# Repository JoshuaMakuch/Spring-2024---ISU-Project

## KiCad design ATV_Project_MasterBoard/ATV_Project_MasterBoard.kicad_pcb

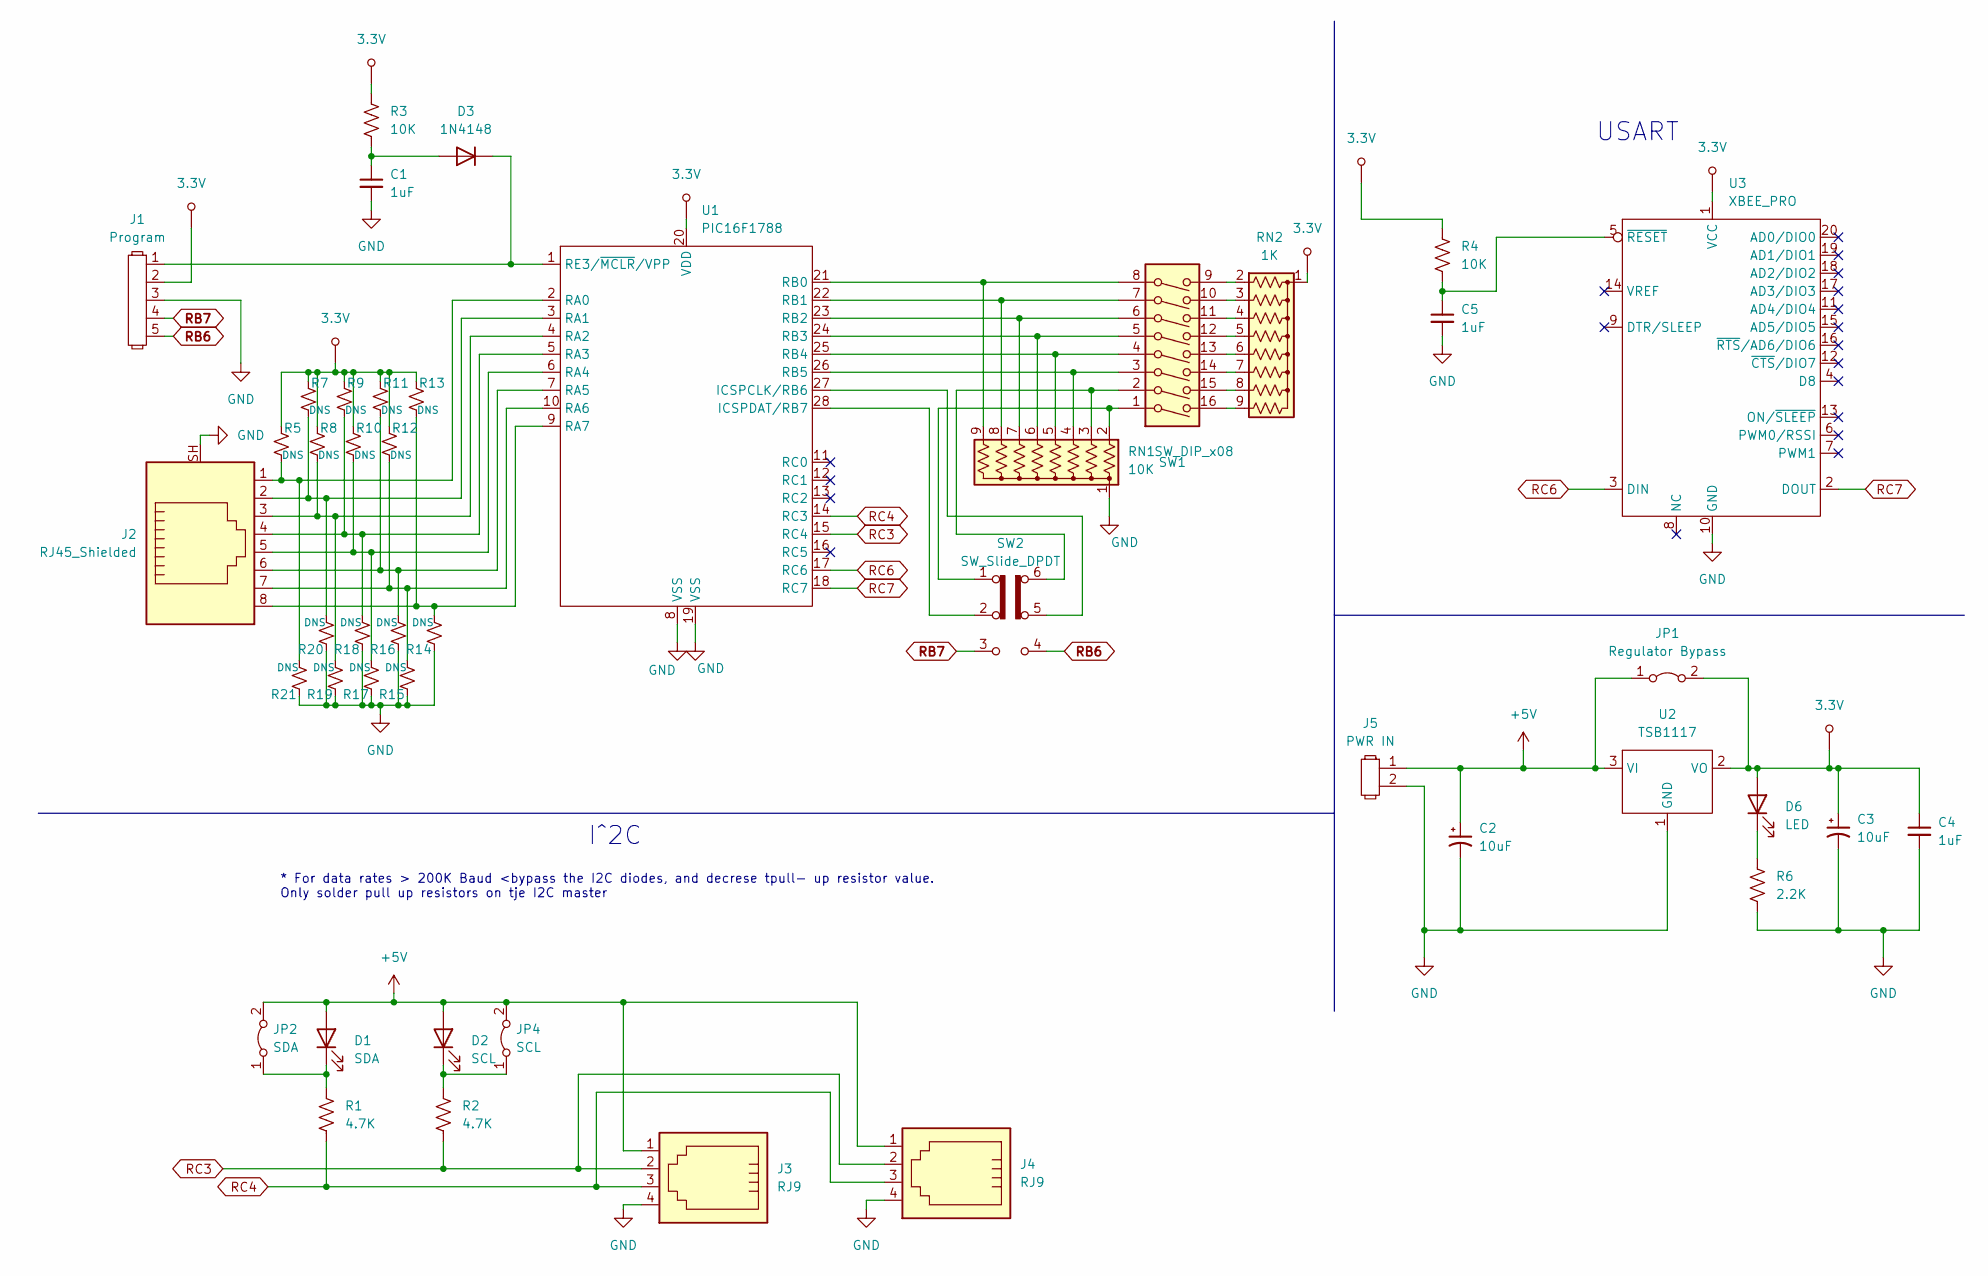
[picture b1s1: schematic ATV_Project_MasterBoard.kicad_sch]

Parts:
C1, C4, C5: 1uF; C_0805_2012Metric_Pad1.18x1.45mm_HandSolder
C2, C3: 10uF; C_0805_2012Metric_Pad1.18x1.45mm_HandSolder
D1: SDA; D_0805_2012Metric_Pad1.15x1.40mm_HandSolder
D2: SCL; D_0805_2012Metric_Pad1.15x1.40mm_HandSolder
D3: 1N4148; D_0805_2012Metric_Pad1.15x1.40mm_HandSolder
D6: LED; D_0805_2012Metric_Pad1.15x1.40mm_HandSolder
J1: Program; PinHeader_1x05_P2.54mm_Vertical
J2: RJ45_Shielded; RJ45_Shieleded_BB
J3, J4: RJ9; RJ11_BB
J5: PWR IN; 2 Pin Header
JP1: Regulator Bypass; PinHeader_1x02_P2.54mm_Vertical
JP2: SDA; PinHeader_1x02_P2.54mm_Vertical
JP4: SCL; PinHeader_1x02_P2.54mm_Vertical
R1, R2: 4.7K; R_0805_2012Metric_Pad1.20x1.40mm_HandSolder
R3, R4: 10K; R_0805_2012Metric_Pad1.20x1.40mm_HandSolder
R5, R7, R8, R9, R10, R11, R12, R13, R14, R15, R16, R17, R18, R19, R20, R21: DNS; R_0805_2012Metric_Pad1.20x1.40mm_HandSolder
R6: 2.2K; R_0805_2012Metric_Pad1.20x1.40mm_HandSolder
RN1: 10K; R_Array_SIP9
RN2: 1K; R_Array_SIP9
SW1: SW_DIP_x08; Dip Switch (16 pin)
SW2: SW_Slide_DPDT; DPDT Switch
U1: PIC16F1788; PIC1788
U2: TSB1117; SOT-223-3_TabPin2
U3: XBEE_PRO; Zigby

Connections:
3.3V: C3.1, C4.1, D6.2 (A), J1.2, JP1.2 (B), R3.1, R4.1, R5.1, R7.1, R8.1, R9.1, R10.1, R11.1, R12.1, R13.1, RN2.1 (common), U1.20 (VDD), U2.2 (VO), U3.1 (VCC)
+5V: C2.1, D1.2 (A), D2.2 (A), J3.1, J4.1, J5.1, JP1.1 (A), JP2.2 (B), JP4.2 (B), U2.3 (VI)
GND: C1.2, C2.2, C3.2, C4.2, C5.2, J1.3, J2.SH, J3.4, J4.4, J5.2, R6.2, R14.1, R15.1, R16.1, R17.1, R18.1, R19.1, R20.1, R21.1, RN1.1 (common), U1.8 (VSS), U1.19 (VSS), U2.1 (GND), U3.10 (GND)
unnamed: D1.1 (K), JP2.1 (A), R1.1
unnamed: D2.1 (K), JP4.1 (A), R2.1
unnamed: C1.1, D3.2 (A), R3.2
unnamed: D3.1 (K), J1.1, U1.1 (RE3/~MCLR/VPP)
unnamed: D6.1 (K), R6.1
unnamed: RN1.2 (R1), SW1.1, SW2.1 (A)
unnamed: RN1.3 (R2), SW1.2, SW2.6 (C)
unnamed: RN1.4 (R3), SW1.3, U1.26 (RB5)
unnamed: RN1.5 (R4), SW1.4, U1.25 (RB4)
unnamed: RN1.6 (R5), SW1.5, U1.24 (RB3)
unnamed: RN1.7 (R6), SW1.6, U1.23 (RB2)
unnamed: RN1.8 (R7), SW1.7, U1.22 (RB1)
unnamed: RN1.9 (R8), SW1.8, U1.21 (RB0)
unnamed: RN2.2 (R1), SW1.9
unnamed: RN2.3 (R2), SW1.10
unnamed: RN2.4 (R3), SW1.11
unnamed: RN2.5 (R4), SW1.12
unnamed: RN2.6 (R5), SW1.13
unnamed: RN2.7 (R6), SW1.14
unnamed: RN2.8 (R7), SW1.15
unnamed: RN2.9 (R8), SW1.16
unnamed: SW2.5 (B), U1.27 (ICSPCLK/RB6)
unnamed: SW2.2 (B), U1.28 (ICSPDAT/RB7)
unnamed: J2.1, R5.2, R21.2, U1.2 (RA0)
unnamed: J2.2, R7.2, R20.2, U1.3 (RA1)
unnamed: J2.3, R8.2, R19.2, U1.4 (RA2)
unnamed: J2.4, R9.2, R18.2, U1.5 (RA3)
unnamed: J2.5, R10.2, R17.2, U1.6 (RA4)
unnamed: J2.6, R11.2, R16.2, U1.7 (RA5)
unnamed: J2.7, R12.2, R15.2, U1.10 (RA6)
unnamed: J2.8, R13.2, R14.2, U1.9 (RA7)
unnamed: C5.1, R4.2, U3.5 (~RESET)
RB6: J1.5, SW2.4 (A)
RB7: J1.4, SW2.3 (C)
RC3: J3.2, J4.2, R2.2, U1.15 (RC4)
RC4: J3.3, J4.3, R1.2, U1.14 (RC3)
RC6: U1.17 (RC6), U3.3 (DIN)
RC7: U1.18 (RC7), U3.2 (DOUT)

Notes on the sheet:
USART
I^2C
* For data rates > 200K Baud <bypass the I2C diodes, and decrese tpull- up resistor value. Only solder pull up resistors on tje I2C master

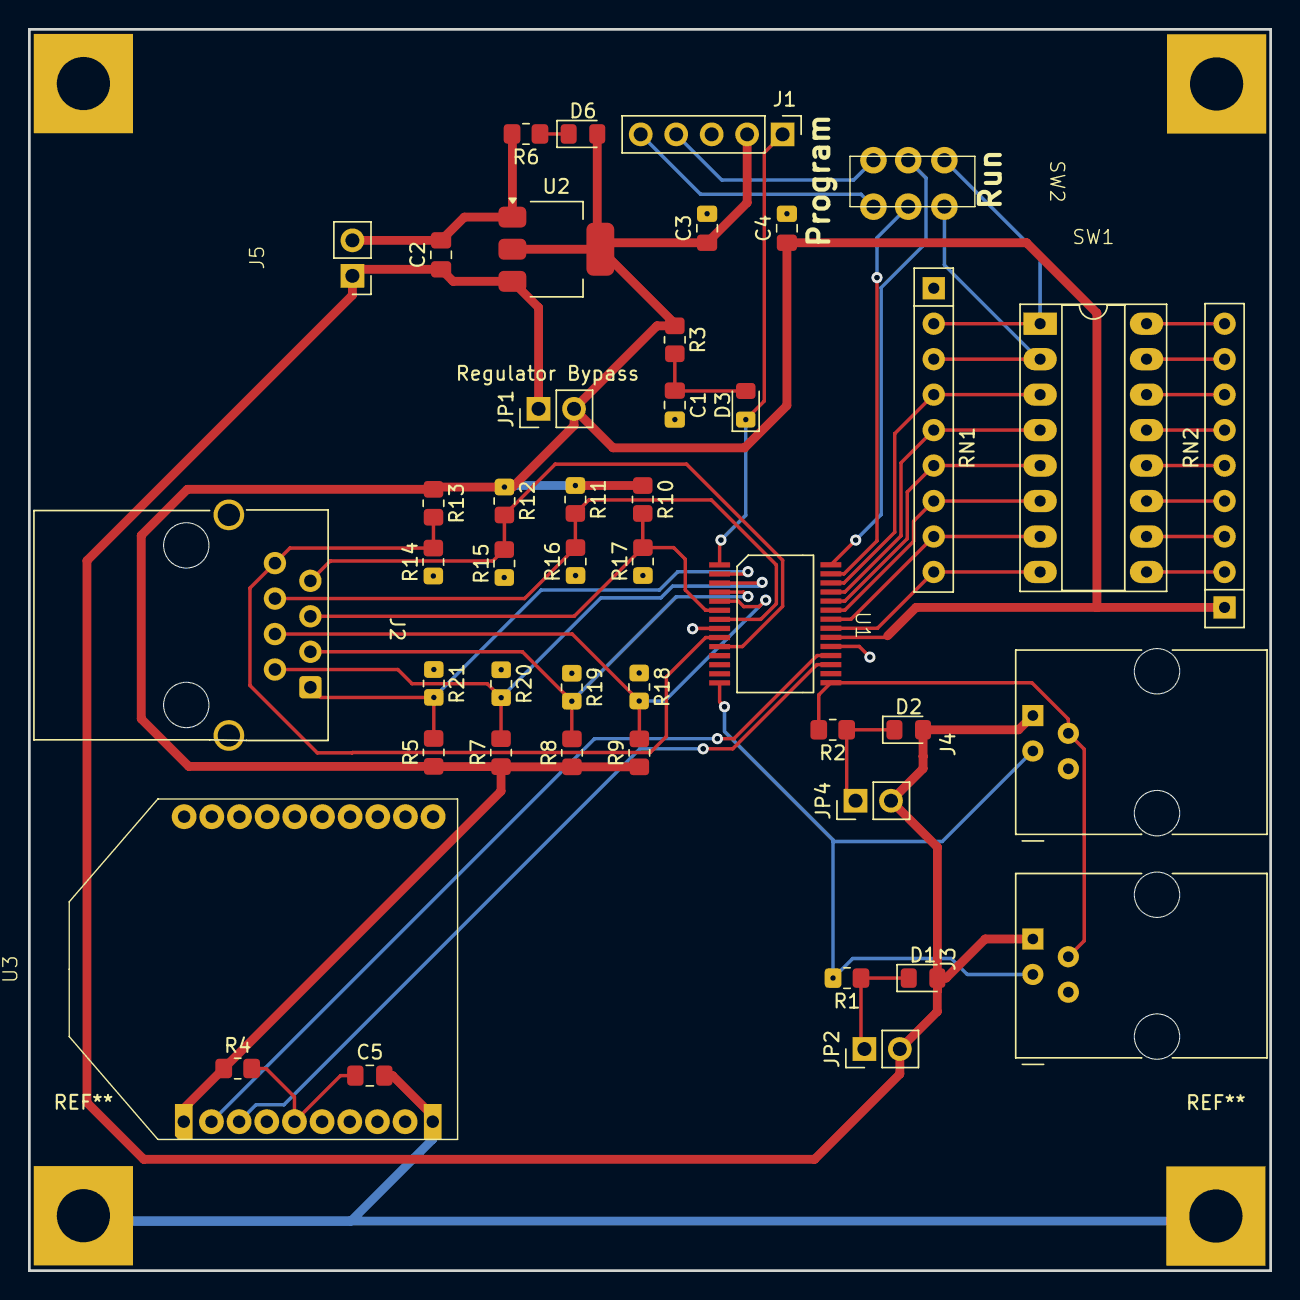
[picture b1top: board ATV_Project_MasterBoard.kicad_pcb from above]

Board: 2 copper layers, 88.9 x 88.9 mm, 45 parts (0 on the bottom side), 41 nets.

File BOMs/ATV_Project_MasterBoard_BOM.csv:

Reference,Value,Datasheet,Footprint,Manufacture Part #,Quanity,1x,100x,Cost Per Board
"C1,C4,C5",1uF,~,Capacitor_SMD:C_0805_2012Metric_Pad1.18x1.45mm_HandSolder,08051C104KAT4A,3,$0.11 ,$0.04 ,0.117
"C2,C3",10uF,~,Capacitor_SMD:C_0805_2012Metric_Pad1.18x1.45mm_HandSolder,C0805C106M8PACTU,2,$0.24 ,$0.08 ,0.152
"D1,JP2",SDA,~,-- mixed values --,TMS-103-02-G-S,2,$0.60 ,$0.37 ,0.74
"D2,JP4",SCL,~,-- mixed values --,SM0805RC,2,$0.20 ,$0.17 ,0.334
D3,1N4148,https://assets.nexperia.com/documents/data-sheet/1N4148_1N4448.pdf,Diode_SMD:D_0805_2012Metric_Pad1.15x1.40mm_HandSolder,1N4148WS-HE3-18,1,$0.23 ,0.067,0.067
D6,LED,~,Diode_SMD:D_0805_2012Metric_Pad1.15x1.40mm_HandSolder,SM0805RC,1,$0.20 ,$0.17 ,0.167
J1,Program,,Connector_PinHeader_2.54mm:PinHeader_1x05_P2.54mm_Vertical,TMS-103-02-G-S,1,$0.60 ,$0.37 ,0.37
J2,RJ45_Shielded,~,footprint library:RJ45_Shieleded_BB,TMJUTVW0021192448,1,$8.91 ,$8.74 ,8.74
"J3,J4",RJ9,~,footprint library:RJ11_BB,73306-111LF,2,$1.68 ,$1.29 ,2.58
J5,PWR IN,,ATVProject_Library:2 Pin Header,TMS-103-02-G-S,1,$0.60 ,$0.37 ,0.37
JP1,Regulator Bypass,~,Connector_PinHeader_2.54mm:PinHeader_1x02_P2.54mm_Vertical,TMS-103-02-G-S,1,$0.60 ,$0.37 ,0.37
"R1,R2",4.7K,~,Resistor_SMD:R_0805_2012Metric_Pad1.20x1.40mm_HandSolder,CRCW08054K70FKEC,2,$0.11 ,$0.02 ,0.044
"R3,R4,RN1",10K,-- mixed values --,-- mixed values --,CR0805-FX-1002ELF,3,$0.10 ,$0.01 ,0.024
"R5,R7,R8,R9,R10,R11,R12,R13,R14,R15,R16,R17,R18,R19,R20,R21",DNS,~,Resistor_SMD:R_0805_2012Metric_Pad1.20x1.40mm_HandSolder,,16,$0.10 ,$0.01 ,0.128
R6,2.2K,~,Resistor_SMD:R_0805_2012Metric_Pad1.20x1.40mm_HandSolder,CR0805-FX-2201ELF,1,,,
RN2,1K,http://www.vishay.com/docs/31509/csc.pdf,Resistor_THT:R_Array_SIP9,CMP0805QFX-1001ELF,1,$0.19 ,$0.06 ,0.059
SW1,SW_DIP_x08,~,ATVProject_Library:Dip Switch (16 pin),,1,$0.10 ,$0.01 ,0.008
SW2,SW_Slide_DPDT,~,ATVProject_Library:DPDT Switch,JS202011CQN,1,$0.64 ,$0.48 ,0.48
U1,PIC16F1788,,ATVProject_Library:PIC1788,PIC16F1788-I/SS,1," 	$2.58",$2.14 ,2.14
U2,TSB1117,,Package_TO_SOT_SMD:SOT-223-3_TabPin2,TPS7B8333QDCYRQ1W,1,$1.56 ,$1.12 ,1.12
U3,XBEE_PRO,,ATVProject_Library:Zigby,XBP9B-XCST-001,1,$58.08 ,$58.08 ,58.08
,,,,,,,,
,,,,,,Cost Per Board,,76.09

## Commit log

2024-05-01 ATV Footprint Library - 2023
2024-05-01 Spare Files
2024-05-01 Drive - Fall 2023
2024-05-01 Create Fall 2023
2024-05-01 Final Report, Presentation, and Informerical
2024-05-01 Presentation
    Infomercial - https://youtu.be/7eZqradmt9g
2024-05-01 BOMs
2024-05-01 Breadboard Pictures
2024-05-01 Comm Pictures
2024-05-01 Kicad Files
2024-05-01 Physical Controller Pictures
2024-05-01 Peripheral Controller BOM
2024-05-01 Schematics
2024-05-01 Overall Block Diagram
2024-05-01 Pictures
2024-05-01 Code - ATVProject_Master.X
2024-05-01 Code - ATVProject_DriveControl.X
2024-05-01 Code - ATV_TurretControl.X
2024-05-01 Code - ATV_Project_MasterBoard
2024-05-01 ATV Slave Board
2024-05-01 KiCad - ATV_Slave_Project
2024-05-01 Letter Of Transmittal
2024-05-01 ATV Footprint Library
2024-05-01 Documentation
2024-05-01 Important Files
2024-05-01 Controller Master Source Files
2024-05-01 Project Images
2024-05-01 Servant Control
